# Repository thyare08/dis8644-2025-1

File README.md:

# dis8644-2025-1-procesos

## Acerca de

* Sigla: DIS8644
* Nombre: Taller de diseño de máquinas electrónicas
* Escuela: Escuela de diseño
* Facultad: Facultad de Arquitectura, Arte y Diseño
* Universidad: Universidad Diego Portales
* Semestre: primer semestre 2025 (marzo a julio)
* Versión: v1.0.0, esta es la primera vez que se dicta este curso.

## Estructuras de repositorios

El trabajo conjunto de este curso es público, y está repartido en 2 repositorios:

* <https://github.com/disenoUDP/dis8644-2025-1-procesos>
  * activo entre principios de marzo 2025 y principios de junio 2025.
  * concentra las bitácoras y encargos de estudiantes del curso, y el primer proyecto grupal.
  * repositorio activo desde principios de marzo 2025, y archivado el 11 de junio 2025 a las 09pm.
* <https://github.com/disenoUDP/dis8644-2025-1-proyectos>:
  * activo entre principios de junio 2025 y principios de julio 2025.
    * concentra las bitácoras y encargos de estudiantes del curso, el segundo proyecto grupal, y el examen grupal.

## equipo docente

* aarón montoya <https://github.com/montoyamoraga/>, profesor titular de taller
* matías serrano <https://github.com/misaaaaaa>, profesor adjunto de taller
* andrés martin <https://github.com/AndresMartinM>, ayudante de taller

## subcarpetas de apuntes

a continuación están los enlaces a las subcarpetas de apuntes este repositorio.

* [00-docentes](./00-docentes/)
* [01-sofiacartes](./01-sofiacartes/)
* [02-hazzaily](./02-hazzaily/)
* [03-antocristi](./03-antocristi/)
* [04-bumwox](./04-bumwox/)
* [05-brauliofigueroa2001](./05-brauliofigueroa2001/)
* [07-antfuentealba](./07-antfuentealba/)
* [08-clifford1one](./08-clifford1one/)
* [09-isabellagutierrezm](./09-isabellagutierrezm/)
* [10-Bernardita-lobo](./10-Bernardita-lobo/)
* [11-Anaisbmg](./11-Anaisbmg/)
* [12-zaaaiko](./12-zaaaiko/)
* [13-jotamorales-romulus](./13-jotamorales-romulus/)
* [15-Camila-Parada](./15-Camila-Parada/)
* [16-sofrito](./16-sofrito/)
* [17-sz-mada](./17-sz-mada/)
* [18-katalinariquelme](./18-katalinariquelme/)
* [19-felix-rg416](./19-felix-rg416/)
* [20-vxlentiinaa](./20-vxlentiinaa/)
* [21-SebastianSaez1003](./21-SebastianSaez1003/)
* [22-thyare08](./22-thyare08/)
* [23-duckusu](./23-duckusu/)
* [24-HSB25](./24-HSB25/)
* [25-FranUDP](./25-FranUDP/)
* [26-paulinavargasf](./26-paulinavargasf/)
* [27-AlanisMria](./27-AlanisMria/)
* [28-IzhakVillegas](./28-IzhakVillegas/)

## sesiones

nuestras sesiones de clases son los martes y viernes entre marzo y julio 2025.

* 08:30am - 09:00am: preparación inicial, resolver dudas
* 09:00am - 10:30am: primera parte, foco contenidos y trabajo grupal de taller
* 10:30am - 11:00am: pausa
* 11:00am - 12:30pm: segunda parte, foco retroalimentación a estudiantes

## calendario detallado

| sesión                        | fecha    | temas                           |
| :---------------------------- | :--------| :-------------------------------|
| [01a](00-docentes/sesion-01a/)| 03-11 mar| presentación equipo             |
| [01b](00-docentes/sesion-01b/)| 03-14 vie| MarkDown, protoboard, caja negra|
| [02a](00-docentes/sesion-02a/)| 03-18 mar| resistores, LEDs, interruptores |
| [02b](00-docentes/sesion-02b/)| 03-21 vie| circuitos serie y paralelo      |
| [03a](00-docentes/sesion-03a/)| 03-25 mar| chips, timer 555, esquemáticos  |
| [03b](00-docentes/sesion-03b/)| 03-28 vie| resist. experimentales, visita MAC |
| [04a](00-docentes/sesion-04a/)| 04-01 mar| trabajo proyecto-01             |
| [04b](00-docentes/sesion-04b/)| 04-04 vie| trabajo proyecto-01             |
| [05a](00-docentes/sesion-05a/)| 04-08 mar| trabajo proyecto-01             |
| [05b](00-docentes/sesion-05b/)| 04-11 vie| trabajo proyecto-01             |
| [06a](00-docentes/sesion-06a/)| 04-15 mar| entrega proyecto-01             |
| [06b](00-docentes/sesion-06b/)| 04-18 vie| no hay clase por feriado        |
| [07a](00-docentes/sesion-07a/)| 04-22 mar| diseño de circuitos en kicad    |
| [07b](00-docentes/sesion-07b/)| 04-25 vie| diseño de circuitos en kicad    |
| [08a](00-docentes/sesion-08a/)| 04-29 mar| diseño de circuitos en kicad    |
| [08b](00-docentes/sesion-08b/)| 05-02 vie| no hay clase por receso         |
| [09a](00-docentes/sesion-09a/)| 05-06 mar| no hay clase por receso         |
| [09b](00-docentes/sesion-09b/)| 05-09 vie| circuitos de PWM                |
| [10a](00-docentes/sesion-10a/)| 05-13 mar| comparadores y opamps           |
| [10b](00-docentes/sesion-10b/)| 05-16 vie| soldar placas udpudu y BOMs     |
| [11a](00-docentes/sesion-11a/)| 05-20 mar| motores y transistores          |
| [11b](00-docentes/sesion-11b/)| 05-23 vie| secuencias con chip 4017        |
| [12a](00-docentes/sesion-12a/)| 05-27 mar| clock, temporizar, secuenciar   |
| [12b](00-docentes/sesion-12b/)| 05-30 vie| repaso  de todo lo aprendido    |

## evaluaciones

la nota de presentación al examen se calcula según el promedio simple de estas 4 notas:

* bitácoras
* encargos
* proyecto-01 grupal
* proyecto-02 grupal

si la nota de presentación es mayor o igual a 4.0, y la asistencia a clases es mayor o igual a 70%, se puede rendir el examen final.

el examen final es tomado por una comisión académica externa.

la nota final del curso se calcula con la siguiente fórmula: TODO.

### sobre la nota de bitácoras

la nota de bitácoras está compuesta de 4 notas.

cada 1 correspondiente a 1 de los meses lectivos:

1. bitácoras marzo
    * tenemos 6 sesiones de clases, NO consideramos las 2 peores bitácoras
2. bitácoras abril
    * tenemos 7 sesiones de clases, NO consideramos las 2 peores bitácoras
3. bitácoras mayo
    * tenemos 7 sesiones de clases, NO consideramos las 2 peores bitácoras
4. bitácoras junio
    * tenemos 8 sesiones de clases, NO consideramos las 2 peores bitácoras

de estas 4 notas de bitácoras, NO consideramos la peor.

así la nota de bitácoras es el promedio de las 3 mejores notas de bitácoras.

cada entrada en las bitácoras se evalúa según esta escala:

* 0.0: inexistente o con muchísimos errores
* 0.3: existente, con muchos errores
* 0.5: cumple, con errores
* 0.7: bueno, con pocos errores
* 1.0: muy bueno, poquísimos errores

además se da retroalimentación escrita a todo el curso sobre cada entrada.

### sobre la nota de encargos

la nota de encargos está compuesta de 4 notas.

cada 1 correspondiente a 1 de los meses lectivos:

1. encargos marzo
    * 10 encargos, NO consideramos los 3 peores encargos.
2. encargos abril
    * 08 encargos, NO consideramos los 2 peores encargos.
3. encargos mayo
    * 14 encargos, NO consideramos los 4 peores encargos.
4. encargos junio
    * TODO encargos, NO consideramos los TODO peores encargos.

de estas 4 notas de encargos, NO consideramos la peor.

así la nota de encargos es el promedio de las 3 mejores notas de encargos.

cada encargo se evalúa

* 0.0: inexistente o con muchísimos errores
* 0.3: existente, con muchos errores
* 0.5: cumple, con errores
* 0.7: bueno, con pocos errores
* 1.0: muy bueno, poquísimos errores

además se da retroalimentación escrita a todo el curso sobre cada nota.

### sobre la nota de proyecto-01

esta nota mide 6 criterios, cada uno se evalúa con nota entre 0.0 y 1.0:

* 0.0: inexistente o con muchísimos errores
* 0.3: existente, con muchos errores
* 0.5: cumple, con errores
* 0.7: bueno, con pocos errores
* 1.0: muy bueno, poquísimos errores

los 6 criterios a evaluar son:

1. introducción, premisa, explicación textual
2. anatomía física, diagramas, ilustraciones, texto
3. bitácora multimedia, proceso
4. esquemático eléctrico, bill of materials, citas y referencias
5. presentación oral, apoyo con bitácora github
6. funcionamiento, robustez electromecánica

### sobre la nota de proyecto-02

info en repositorio <https://github.com/disenoUDP/dis8644-2025-1-proyectos>

### sobre la nota de examen final

info en repositorio <https://github.com/disenoUDP/dis8644-2025-1-proyectos>

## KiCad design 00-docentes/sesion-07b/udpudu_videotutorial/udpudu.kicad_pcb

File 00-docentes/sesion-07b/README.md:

# sesion-07b

viernes 25 de abril 2025

Cada componente físico tiene:

- Nombre

Nomina el tipo de componente: por ejemplo

    Resistencia
    
    Condensador
    
    Circuito Integrado
    
    Transistor

- Valor

"Apellido" del componente, que alude a su cantidad numérica o su funcionalidad: por ejemplo

    100k ohm (de una resistencia)
    
    10 uF (de un condensador)
    
    NE555P (de un Circuito Integrado)
    
    2n2222A (de un Transistor)

- Encapsulado

Forma física del componente, que depende de otras características, como de espacio o la necesidad de disipación térmica. Para saber más sobre encapsulados, puedes googlear la palabra "Package"

    Axial 1/4 w 6.5mm (Resistencia de 100k)
    
    Radial D6.3 mm P 2.5mm (Condensador electrolítico de 10uF con ese tamaño)
    
    DIP-8 (Circuito integrado de 8 pines de tipo THT)

    TO-92 (Para transitor de valor 2n2222A)

## encargo-16: cotizar udpudu en JLCPCB de forma productiva

hacerse una cuenta en JLCPCB y cotizar udpudu, para 30 personas, documentar cada parámetro y elección.

## encargo-17: cotizar udpudu en JLCPCB de forma experimental

probar opciones que no entiendan, documentar otros parámetros que no conozcan aún.

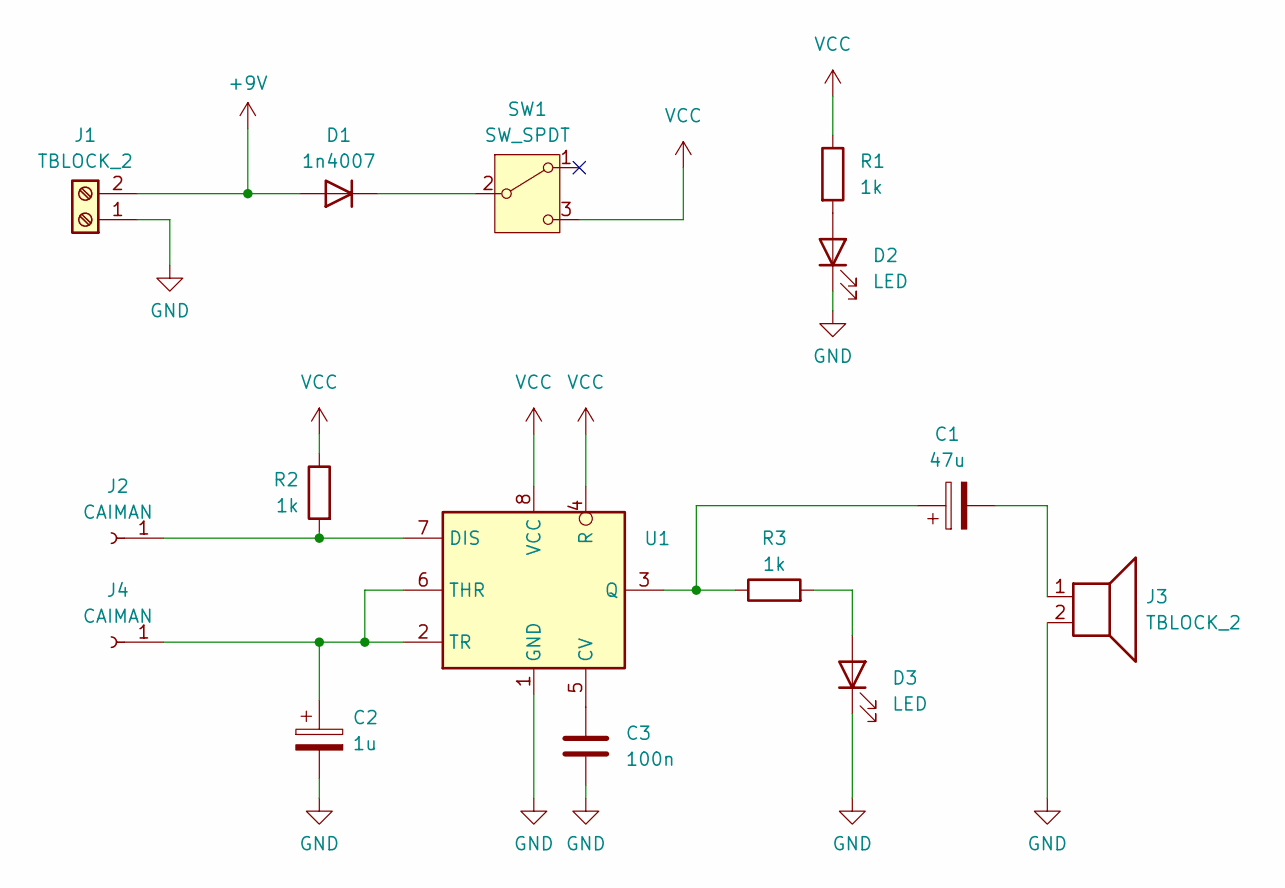
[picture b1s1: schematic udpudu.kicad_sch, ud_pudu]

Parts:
C1: 47u; CP_Radial_D6.3mm_P2.50mm
C2: 1u; CP_Radial_D6.3mm_P2.50mm
C3: 100n; C_Disc_D6.0mm_W2.5mm_P5.00mm
D1: 1n4007; D_DO-41_SOD81_P10.16mm_Horizontal
D2, D3: LED; LED_D5.0mm
J1, J3: TBLOCK_2; TerminalBlock_MaiXu_MX126-5.0-02P_1x02_P5.00mm
J2, J4: CAIMAN; caiman
R1, R2, R3: 1k; R_Axial_DIN0207_L6.3mm_D2.5mm_P10.16mm_Horizontal
SW1: SW_SPDT; SPDT_PCB_small_P2.5mm
U1: DIP-8_W7.62mm_Socket_LongPads

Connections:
+9V: D1.2 (A), J1.2
GND: C2.2, C3.2, D2.1 (K), D3.1 (K), J1.1, J3.2, U1.1 (GND)
unnamed: C1.2, J3.1
unnamed: D1.1 (K), SW1.2 (B)
unnamed: D2.2 (A), R1.2
unnamed: D3.2 (A), R3.2
unnamed: J2.1, R2.2, U1.7 (DIS)
unnamed: C2.1, J4.1, U1.2 (TR), U1.6 (THR)
unnamed: C3.1, U1.5 (CV)
unnamed: C1.1, R3.1, U1.3 (Q)
VCC: R1.1, R2.1, SW1.3 (C), U1.4 (R), U1.8 (VCC)

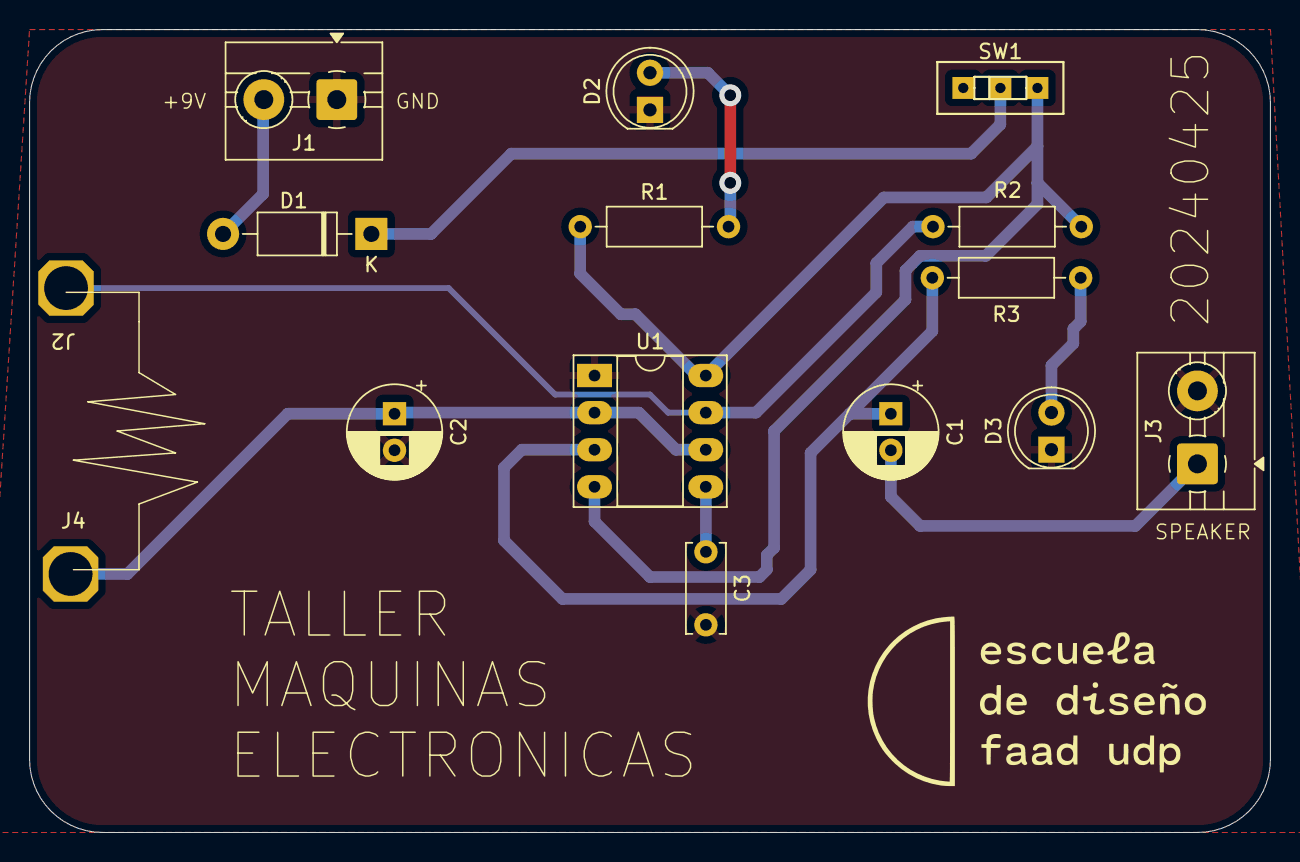
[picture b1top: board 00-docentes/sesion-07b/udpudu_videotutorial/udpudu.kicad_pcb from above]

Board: 2 copper layers, 85.0 x 55.0 mm, 15 parts (0 on the bottom side), 11 nets.

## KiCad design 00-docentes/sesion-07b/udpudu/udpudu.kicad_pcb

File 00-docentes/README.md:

# enlaces

- [sesion-01-a](./sesion-01-a)
- [sesion-01-b](./sesion-01-b)
- [sesion-02-a](./sesion-02-a)
- [sesion-02-b](./sesion-02-b)
- [sesion-03-a](./sesion-03-a)
- [sesion-03-b](./sesion-03-b)
- [sesion-04-a](./sesion-04-a)
- [sesion-04-b](./sesion-04-b)
- [sesion-05-a](./sesion-05-a)
- [sesion-05-b](./sesion-05-b)
- [sesion-06-a](./sesion-06-a)
- [sesion-06-b](./sesion-06-b)
- [sesion-07-a](./sesion-07-a)
- [sesion-07-b](./sesion-07-b)
- [sesion-08-a](./sesion-08-a)
- [sesion-08-b](./sesion-08-b)
- [sesion-09-a](./sesion-09-a)
- [sesion-09-b](./sesion-09-b)
- [sesion-10-a](./sesion-10-a)
- [sesion-10-b](./sesion-10-b)
- [sesion-11-a](./sesion-11-a)
- [sesion-11-b](./sesion-11-b)
- [sesion-12-a](./sesion-12-a)
- [sesion-12-b](./sesion-12-b)
- [sesion-13-a](./sesion-13-a)
- [sesion-13-b](./sesion-13-b)
- [sesion-14-a](./sesion-14-a)
- [sesion-14-b](./sesion-14-b)
- [sesion-15-a](./sesion-15-a)
- [sesion-15-b](./sesion-15-b)

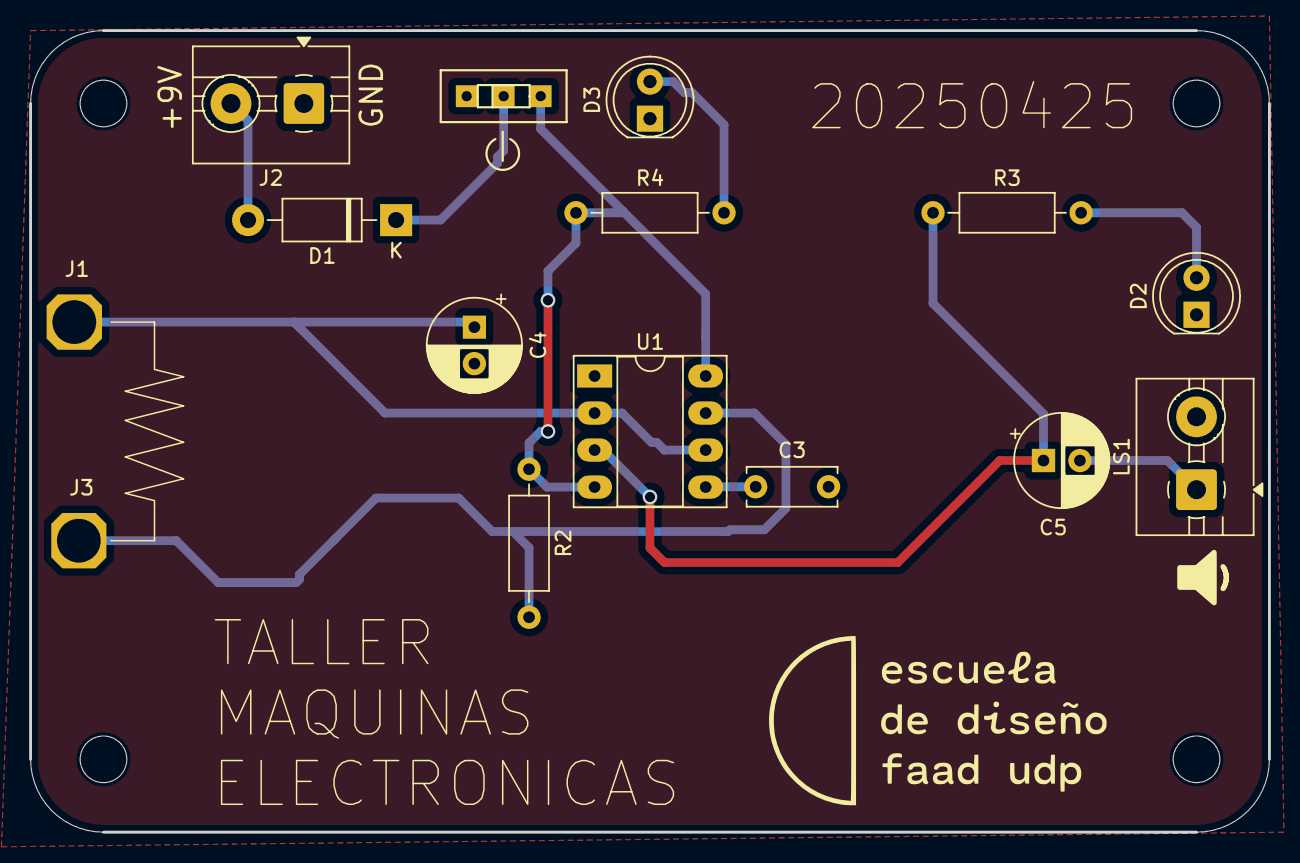
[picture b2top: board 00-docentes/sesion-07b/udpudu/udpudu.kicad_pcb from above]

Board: 2 copper layers, 85.0 x 55.0 mm, 19 parts (0 on the bottom side), 11 nets.

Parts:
C3: 100n; C_Disc_D6.0mm_W2.5mm_P5.00mm
C4: 1u; CP_Radial_D6.3mm_P2.50mm
C5: 47u; CP_Radial_D6.3mm_P2.50mm
D1: 1n4007; D_DO-41_SOD81_P10.16mm_Horizontal
D2, D3: LED; LED_D5.0mm
H1, H2, H3, H4: MountingHole; MountingHole_3.2mm_M3
J1, J3: CAIMAN; caiman
J2: TBLOCK_2; TerminalBlock_MaiXu_MX126-5.0-02P_1x02_P5.00mm
LS1: SPK; TerminalBlock_MaiXu_MX126-5.0-02P_1x02_P5.00mm
R2, R3, R4: 1k; R_Axial_DIN0207_L6.3mm_D2.5mm_P10.16mm_Horizontal
SW1: SW_SPDT; SPDT_PCB_small_P2.5mm
U1: DIP-8_W7.62mm_Socket_LongPads

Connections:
+9V: D1.2 (A), J2.2
GND: C3.2, C4.2, D2.1 (K), D3.1 (K), J2.1, LS1.2, U1.1 (GND)
unnamed: C5.2, LS1.1
unnamed: D1.1 (K), SW1.2 (B)
unnamed: D2.2 (A), R3.2
unnamed: D3.2 (A), R4.2
unnamed: C4.1, J1.1, U1.2 (TR), U1.6 (THR)
unnamed: J3.1, R2.2, U1.7 (DIS)
unnamed: C3.1, U1.5 (CV)
unnamed: C5.1, R3.1, U1.3 (Q)
VCC: R2.1, R4.1, SW1.3 (C), U1.4 (R), U1.8 (VCC)

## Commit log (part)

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2025-06-09 corregir MD022 de isabellagutierrezm y MD025 y MD033 de zaaaiko
2025-06-10 README.md
2025-06-10 listo
2025-06-10 encargo pcb
2025-06-10 66% encargos pcbs
2025-06-10 mover archivos
2025-06-10 cambios varios
2025-06-10 arregla error-github actions
2025-06-10 Rename 4017-diagrama.jpeg to 4017-diagrama.jpg
2025-06-10 corregir errores MD de thyare08
2025-06-10 corregir errores MD033 y MD066 de Camila-Parada
2025-06-10 Archivos subidos
2025-06-10 agregar error MD040 de isabellagutierrezm
2025-06-10 borrar algunos whitespace
2025-06-10 linting automatico
2025-06-10 retroalimentacion
2025-06-11 agregar retroalimentacion FranUDP
2025-06-11 borrar archivo
2025-06-11 agregar retroalimentacion SebastianSaez1003
2025-06-11 agregar retroalimentacion
2025-06-11 agregar lint
2025-06-11 Rename ERSA ICON-NANO-ICON-PICO DATA-SHEET.pdf to ERSA-DATA-SHEET.pdf
2025-06-11 Rename NA555.PDF to NA555.pdf
2025-06-11 encargo 18
2025-06-11 laurie anderson
2025-06-11 arreglar codigos vacios 10b
2025-06-11 ordenar README
2025-06-11 agregar descripciones sesiones 11a 11b 12a 12b
2025-06-12 encargo udpudu-soldar-p1
2025-06-12 Apuntes 12b
